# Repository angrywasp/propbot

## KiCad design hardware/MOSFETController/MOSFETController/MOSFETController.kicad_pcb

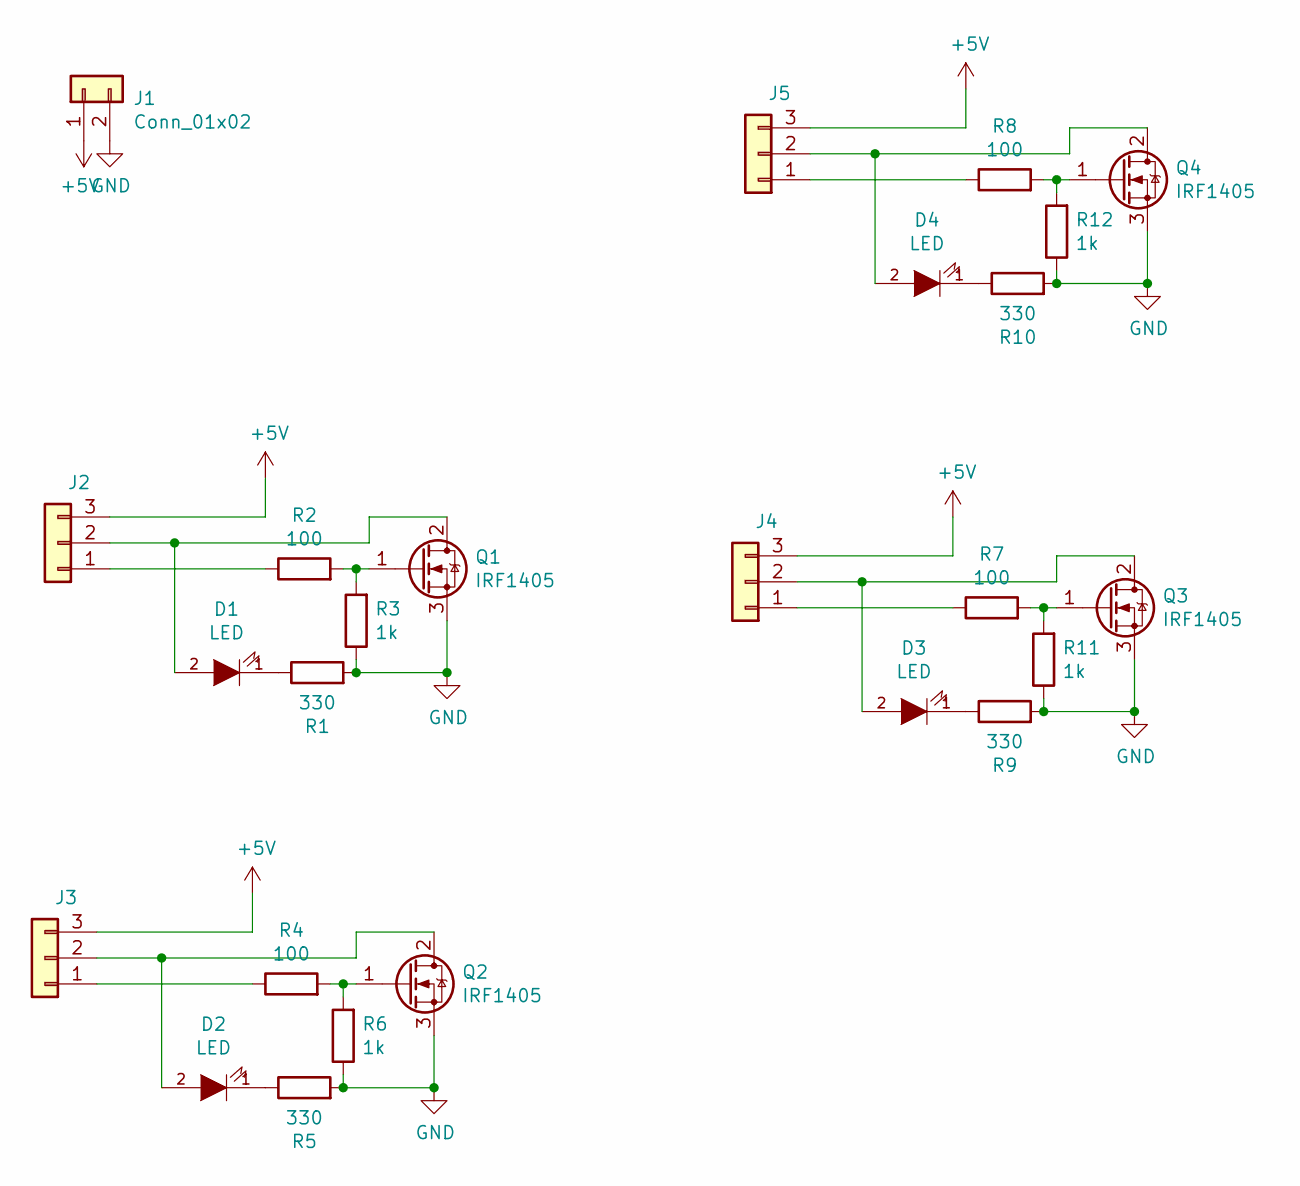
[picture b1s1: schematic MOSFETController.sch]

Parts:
D1, D2, D3, D4: LED; LED_0805_HS
J1: Conn_01x02; Pin_Header_Circular_1x02
J2, J3, J4, J5: Conn_01x03; Pin_Header_Circular_1x03
Q1, Q2, Q3, Q4: IRF1405; TO-220-3_Horizontal_TabDown
R1, R5, R9, R10: 330; 0805_HS
R2, R4, R7, R8: 100; 0805_HS
R3, R6, R11, R12: 1k; 0805_HS

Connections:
+5V: J1.1, J2.3, J3.3, J4.3, J5.3
GND: J1.2, Q1.3 (S), Q2.3 (S), Q3.3 (S), Q4.3 (S), R1.2, R3.1, R5.2, R6.1, R9.2, R10.2, R11.1, R12.1
unnamed: D1.1 (K), R1.1
unnamed: D1.2 (A), J2.2, Q1.2 (D)
unnamed: D2.1 (K), R5.1
unnamed: D2.2 (A), J3.2, Q2.2 (D)
unnamed: D3.1 (K), R9.1
unnamed: D3.2 (A), J4.2, Q3.2 (D)
unnamed: D4.1 (K), R10.1
unnamed: D4.2 (A), J5.2, Q4.2 (D)
unnamed: J2.1, R2.1
unnamed: J3.1, R4.1
unnamed: J4.1, R7.1
unnamed: J5.1, R8.1
unnamed: Q1.1 (G), R2.2, R3.2
unnamed: Q2.1 (G), R4.2, R6.2
unnamed: Q3.1 (G), R7.2, R11.2
unnamed: Q4.1 (G), R8.2, R12.2

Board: 2 copper layers, 25 parts (0 on the bottom side), 18 nets, no tracks yet.
